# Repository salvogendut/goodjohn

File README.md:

# Goodjohn

Goodjohn is a Raspberry Pi Pico interface for using an Amstrad CPC keyboard as
a USB keyboard on a PC. This repository holds the firmware, wiring guides and
a prototype Pico carrier PCB.

> [!WARNING]
> **USB keyboard use only.** Physically disconnect the keyboard from the CPC
> motherboard before connecting it to the Pico, even if the CPC is powered off.
> **The keyboard cannot operate the CPC and the PC at the same time.** This
> interface does not provide simultaneous use or a pass-through connection to
> the CPC. Switching the CPC off is not a substitute for disconnecting it.

The first prototype uses an **original RP2040 Pico**, an **English CPC/QWERTY
keyboard**, and **exclusive control of a keyboard disconnected from the CPC
motherboard**. These are the agreed initial requirements. The passive keyboard
connects to Pico GPIO; the Pico's USB connector connects to the PC.

The drawing's **J1 adapter connector** uses the contact numbering of Bread80's
CPC464 **J3 keyboard connector**. Its square contact 1 is shown at the bottom;
labels give **GPIO / physical Pico pin**. See the [pinout sheet](docs/pinout.pdf)
for connector checks and assembly details.

**Original CPC464 PCB-style keyboard:** use the inline wiring above. Its
19-signal connector pinout is shared by rgbwalker's keyboard and Bread80's
CPC464 SMT **J3** connector. Some versions use a 20-position footprint with one
unused contact. Later CPC464 membrane keyboards use the two-ribbon connection
described below; connector orientation must still be checked on the actual board.

## Current state

There is a buildable C firmware foundation using the Raspberry Pi Pico SDK and
TinyUSB, plus native tests. It scans the physical 10-by-9 CPC464 wiring, debounces
each contact for 5 ms, and sends standard USB HID boot-keyboard reports. The
default scan period is 1 ms. Reports support six regular keys plus modifiers;
more regular keys produce HID ErrorRollOver until the count falls back to six.

Boards without diodes use conservative ghost suppression: new presses in an
ambiguous rectangle are blocked, while already accepted keys and unrelated keys
continue to work. This cannot recover arbitrary chords or detect a release that
is electrically hidden by other held keys. Fully diode-isolated boards can turn
the filter off at build time.

**Status: host tests pass; basic typing works on rgbwalker V1.2.** On 2026-10-06,
the user confirmed the complete number row (`1234567890`), all three letter rows,
Esc and main Enter with the completed 19-wire direct harness. Replacing the
earlier ribbon/jumper path resolved the incorrect characters using the existing
firmware and pin map. The exact fault in that earlier assembly is still unknown.
See the [staged wiring checks and test record](docs/wiring.md#staged-bring-up-for-rgbwalker-v12).

The remaining individual keys, modifiers, chords, cable timing, and USB
suspend/resume and current still need recorded bench tests. The carrier PCB
below is designed and checked, but has not been manufactured or bench-tested.

## Pico carrier PCB prototype

The [v1 carrier](hardware/pico-carrier-v1/README.md) is an **80 × 66 mm, two-layer
board** with a socketed RP2040 Pico, the inline 19-pin connector and separate
10-pin ribbon A/B headers. Use one keyboard through **J1 OR J2 + J3**. It keeps
the tested firmware pin map and powers the Pico through its existing USB port.

The [KiCad project](hardware/pico-carrier-v1/goodjohn-carrier.kicad_pro),
[schematic PDF](hardware/pico-carrier-v1/docs/schematic.pdf),
[assembly guide](hardware/pico-carrier-v1/docs/assembly.pdf),
[BOM](hardware/pico-carrier-v1/bom.csv) and
[Gerber/drill ZIP](hardware/pico-carrier-v1/fabrication/goodjohn-carrier-v1-gerbers.zip)
are included. ERC, DRC and schematic/PCB parity checks pass; an independent
pin-map check matches all 19 signals to the firmware and existing wiring SVGs.
**This is an unbuilt prototype, and the CPC motherboard must remain physically
disconnected.** The carrier headers accept 2.54 mm mating harnesses; bare
membrane tails need an appropriate connector adapter.

## Keyboard projects

| Project | Initial integration |
| --- | --- |
| [rgbwalker's CPC464 Cherry keyboard](https://github.com/rgbwalker/Amstrad_CPC_464_new_Cherry_Keyboard) | V1.2: digits, all letter rows, Esc and main Enter confirmed with a direct 19-wire harness. Further key/chord tests pending; retain ghost suppression. |
| [Bread80 CPC464 SMT mechanical keyboard](https://github.com/Bread80/CPC_Keyboards/tree/main/Keyswitch_CPC464_SMT) | J3 inline and J1 two-ribbon schemes traced from the KiCad PCB. J1 uses CPC464 link settings; hardware validation pending. Verified per-key diodes allow disabling ghost suppression. |
| [Bread80 tactile keyboard](https://github.com/Bread80/CPC_Keyboards/tree/main/Tactile) | Same CPC key arrangement, no diodes; connector adapter still needs checking. |
| [Bread80 CPC6128 SMT keyboard](https://github.com/Bread80/CPC_Keyboards/tree/main/Keyswitch_CPC6128_SMT) | Upstream describes this as a design-stage board; not a validated adapter target. |

Start with [the wiring notes](docs/wiring.md). Connector families are not
interchangeable just because the logical CPC matrix is the same.

For the workbench, use the [ASCII pinout sheet](docs/pinout.txt) or the
[four-page printable PDF](docs/pinout.pdf). These include the Bread80 J3 wire
list, a full Pico header diagram, assembly steps and continuity checks, plus
V1.2 connector orientation and a direct two-wire test for rgbwalker. Regenerate
both with `python3 scripts/generate_pinout.py` after installing
`scripts/requirements-docs.txt` in a Python virtual environment.
Regenerate the README's [SVG wiring diagram](docs/wiring.svg) with
`python3 scripts/generate_wiring_svg.py` in the same environment. It reuses the
Pico artwork from the supplied [pico-pinout.svg](pico-pinout.svg) and the same
firmware-derived wiring data as the sheets.

### Alternate connection: two 10-pin ribbons

Bread80's **CPC464 SMT keyboard J1**, configured for CPC464, can use two 10-way
ribbons with the existing Pico GPIO assignments. Bridge **LK1 pads 1-2** and
**LK2 pads 1-2**; leave **LK3 and the bonus links open**. This alternate harness
is source-checked and has not yet been bench-tested.

The diagram distinguishes ribbon positions from J1 PCB pad numbers. **J1 pad 19
is unused; pad 20 is connected.** Here J1 refers to Bread80's keyboard connector.
Use the [complete wiring scheme and orientation guide](docs/wiring-dual-ribbon.md),
[ASCII pinout](docs/pinout-dual-ribbon.txt), or [two-page PDF](docs/pinout-dual-ribbon.pdf).
This mapping is specific to the CPC464 setting; CPC6128 and Tactile connectors
need separate mappings. Regenerate these files with
`python3 scripts/generate_dual_ribbon.py` in the same documentation environment.

### Original CPC464 keyboard PCB

The original CPC464 keyboard PCB with the inline 19-wire connection is also
expected to work: its passive switch matrix matches the arrangement targeted
by this firmware, as shown in the
[Amstrad service manual](https://retronik.silicium.org/DOCUMENTS/Info/Amstrad_CPC/Amstrad%20CPC464%20CTM640%20GT64%20Service%20Manual.pdf).
The existing keymap should apply to the English/QWERTY version.

Disconnect the keyboard from the CPC motherboard, even when the CPC is powered
off; the Pico takes over keyboard scanning. Verify your connector's numbering,
orientation and switch continuity against the wiring notes before connecting it.
Keep `GOODJOHN_MATRIX_HAS_DIODES=OFF` (the default), since the original matrix
lacks per-key diodes and needs ghost suppression. Compatibility is expected but
has not yet been tested on original hardware; other connector revisions may
require a different harness.

## Build

Prerequisites: CMake, Make or Ninja, Python 3, an Arm bare-metal GCC toolchain
(`arm-none-eabi-gcc` and `arm-none-eabi-g++`), and the Pico SDK. A native C++
compiler is also needed if the SDK builds picotool instead of using an installed
copy. The development build was checked with SDK **2.2.0**, its pinned TinyUSB
submodule, Arm GNU **14.2.Rel1**, and picotool **2.3.1**.

For an SDK checkout outside this repository:

```sh
git clone --branch 2.2.0 --depth 1 https://github.com/raspberrypi/pico-sdk.git ../pico-sdk
git -C ../pico-sdk submodule update --init --depth 1 lib/tinyusb
cmake -S . -B build -DPICO_SDK_PATH="$(pwd)/../pico-sdk" -DPICO_BOARD=pico -DCMAKE_BUILD_TYPE=Release
cmake --build build --parallel
```

Put the compiler's `bin` directory on `PATH`, or set
`-DPICO_TOOLCHAIN_PATH=/path/to/arm-toolchain`. CMake uses an installed picotool
when available (`-Dpicotool_DIR=/path/to/picotool/cmake-directory`); otherwise the
SDK downloads and builds it, which needs network access.

The output is `build/goodjohn.uf2`. Hold BOOTSEL while connecting the Pico over
USB, then copy the UF2 to its `RPI-RP2` volume. This replaces the existing Pico
application. No hardware has been flashed as part of the initial setup.

For a board with verified diodes on every connected switch:

```sh
cmake -S . -B build -DGOODJOHN_MATRIX_HAS_DIODES=ON
cmake --build build --parallel
```

Leave this option OFF for original membranes, the rgbwalker Cherry board, and
the Bread80 tactile board. Edit `src/board_config.h` to change the GPIO wiring.

The default USB VID/PID (`CAFE:4011`) are development placeholders, not an
assignment to this project. A distributed product needs an authorized pair,
set using `GOODJOHN_USB_VID` and `GOODJOHN_USB_PID` CMake variables.

## Initial key behavior

The keymap sends PC key usages, not CPC character codes. Select the desired PC
keyboard layout in the host OS. Letters and digits follow English QWERTY, but
shifted symbols are not guaranteed to match the CPC legends.

| CPC key | PC behavior |
| --- | --- |
| DEL / CLR | Backspace / forward Delete |
| Main Enter / keypad Enter | Enter / keypad Enter |
| COPY | Left Alt |
| Either Shift | Left Shift (both switches share one matrix contact) |
| CTRL / CAPS LOCK | Left Control / Caps Lock |
| Numeric keypad | PC keypad usages; Num Lock state is controlled by the host |
| `^ £` / `- =` / `@ \|` | PC Equal / Minus / Grave key positions |
| `; +` / `: *` | PC Semicolon / Apostrophe key positions |
| Bread80 bonus switches | Unmapped initially |

There is no Fn layer yet, so F1–F12, GUI and Num Lock have no default bindings.
For early testing, set Num Lock using the PC's existing or on-screen keyboard.
The map lives in `src/keymap.c`; exact CPC symbol translation and additional
layouts are separate follow-up work. Host lock LED reports are accepted, but no
physical lock LEDs or USB remote wakeup are implemented.

## Test without a Pico SDK

```sh
cmake -S . -B build-host -DGOODJOHN_HOST_TESTS=ON
cmake --build build-host
ctest --test-dir build-host --output-on-failure
```

These tests cover contact bounce, independent debounce clocks, timer wrap,
ambiguous chords and recovery, the separate DEL column, modifier reports,
keypad Enter, and six-key overflow/recovery. They do not simulate USB hardware.

## Next hardware milestone

1. Pick the exact keyboard PCB revision and verify the connector with a meter.
2. Wire a Pico prototype and check single keys, modifiers, DEL, both Enter keys,
   press/release bounce and multi-key chords on a PC.
3. Measure scan settling with the intended cable, check suspend/resume and
   reconnect behavior, and settle the missing PC-key bindings.
4. Capture the proven wiring in an interface schematic and PCB with appropriate
   connector orientation, protection and optional lock LEDs.

## References

The adjacent keyboard projects are reference inputs and retain their respective
licenses; no upstream PCB or image assets are copied into this repository.
Exact local revisions and electrical findings are recorded in
[the wiring notes](docs/wiring.md).

Firmware references: [Pico SDK 2.2.0](https://github.com/raspberrypi/pico-sdk/tree/2.2.0),
[Raspberry Pi's USB HID example](https://github.com/raspberrypi/pico-examples/tree/master/usb/device/dev_hid_composite),
[TinyUSB](https://docs.tinyusb.org/), and
[Pico board documentation](https://www.raspberrypi.com/documentation/microcontrollers/pico-series.html).

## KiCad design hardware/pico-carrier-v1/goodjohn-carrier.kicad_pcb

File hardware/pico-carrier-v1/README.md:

# Goodjohn Pico carrier v1

An **80 × 66 mm, two-layer, hand-solderable carrier** for an original RP2040
Raspberry Pi Pico / Pico H. It replaces the tested direct jumper wiring with
PCB tracks and offers both CPC464 connector arrangements. The existing firmware
and GPIO assignments apply without changes.

**Status: unbuilt prototype.** KiCad 10.0.6 ERC and DRC pass with zero violations,
zero unconnected items and zero schematic parity issues. The actual schematic
and PCB nets also match the firmware and both existing wiring diagrams. This
PCB has not been manufactured or bench-tested; the earlier successful typing
test used a direct harness with rgbwalker V1.2.

> [!WARNING]
> **USB keyboard only. Physically disconnect the keyboard from the CPC
> motherboard, even when the CPC is powered off.** The keyboard cannot operate
> the CPC and PC simultaneously. This carrier has no switching, isolation or
> CPC pass-through circuitry. Connect one keyboard using **J1 OR J2 + J3**.

The image is a KiCad render, not a photograph of manufactured hardware.

## Files to use

- Open [goodjohn-carrier.kicad_pro](goodjohn-carrier.kicad_pro) in **KiCad 10**.
  The [schematic](goodjohn-carrier.kicad_sch), [routed PCB](goodjohn-carrier.kicad_pcb),
  project-local symbol/footprint libraries and library tables are included.
- Read the [schematic PDF](docs/schematic.pdf), [assembly PDF](docs/assembly.pdf),
  [component-side SVG](docs/assembly-top.svg) and [complete connector CSV](docs/connections.csv).
- Prototype manufacturing package:
  [Gerber + drill ZIP](fabrication/goodjohn-carrier-v1-gerbers.zip),
  [individual files](fabrication/gerbers), [fabrication notes](fabrication/README.md).
- [BOM](bom.csv), [pin-map verification](checks/pinmap.json),
  [ERC report](checks/erc.json), [DRC report](checks/drc.json).

## Connections and orientation

All three keyboard headers are ordinary **2.54 mm single-row male headers**.
Use a continuity-checked mating cable or adapter. They are not native FFC/FPC
sockets for inserting a bare original membrane tail.

With the carrier component side facing you and the Pico USB socket at the top:

| Carrier connector | Placement and pin 1 | Keyboard connection |
| --- | --- | --- |
| **U1** | Pico at left; physical pin 1 upper left, pin 40 upper right | Two 1×20 female sockets, rows 17.78 mm apart; USB faces the upper board edge |
| **J1** | 1×19 at right; **pin 1 is at the bottom**, pin 19 at the top | Inline 19-signal pinout: rgbwalker V1.2, Bread80 CPC464 SMT **J3**, original CPC464 PCB-style keyboard |
| **J2 / A** | Right-hand 1×10 ribbon header; **pin 1 at top** | Ribbon A, Bread80 keyboard **J1 odd pads** 1, 3, …, 19 |
| **J3 / B** | Left-hand 1×10 ribbon header; **pin 1 at top** | Ribbon B, Bread80 keyboard **J1 even pads** 2, 4, …, 20 |

Carrier reference names differ from keyboard reference names. **Follow contact
numbers, not apparent left-to-right order, ribbon colors or connector names.**
Match square pad 1 at both ends. The inline carrier header is intentionally
opposite in vertical numbering to the keyboard's Esc-end pin 1; a cable must
still connect contact 1 to contact 1, 2 to 2, and so on.

For Bread80's **two-ribbon J1 connection in CPC464 mode**, bridge keyboard
**LK1 pads 1–2** and **LK2 pads 1–2**; leave **LK3 and bonus links open**.
Carrier **J2.10 / A10 / keyboard J1.19 is unused**.
Carrier **J3.10 / B10 / keyboard J1.20 is required** and carries Y1.
These link settings belong to the keyboard PCB; there are no links to set on
the carrier. For the inline Bread80 J3 connection, retain the original
[inline wiring instructions](../../docs/wiring.md).

On rgbwalker V1.2 the optional twentieth contact is unused. Do not confuse that
contact with Bread80 two-ribbon J1 pad 20. Original keyboard compatibility is
expected from the pinout but has not been bench-tested. CPC6128 and Bread80
Tactile connectors are not validated targets for this carrier.

The 19 contacts carry matrix signals only. No keyboard contact connects to
ground, 3.3 V or 5 V. Ground planes join only the Pico's GND header pins.
Unused Pico GPIO, AGND, VBUS, VSYS, 3V3 and control pins have isolated pads.
The Pico receives power and exchanges data over **one USB data cable to the PC**;
no second USB port or hub is required. This simple carrier adds no input
protection or motherboard isolation; attach the harness with USB unplugged.

## Parts and assembly

The [BOM CSV](bom.csv) specifies generic mechanical requirements rather than
unverified supplier part numbers. Before buying, compare actual connector
drawings and socket height with the supplied footprints and assembly drawing.

| Item | Quantity | Specification |
| --- | ---: | --- |
| Carrier PCB | 1 | Two layers, 1.6 mm FR4, 35 µm / 1 oz copper |
| U1 module | 1 | Original RP2040 Pico with downward male headers, or Pico H; not a bare RP2040 chip |
| U1 sockets | 2 | 1×20 female, vertical, 2.54 mm pitch; 17.78 mm row spacing; nominal 8.5 mm body height |
| J1 | 1 | 1×19 male, vertical, 2.54 mm pitch, 0.64 mm square posts |
| J2, J3 | 2 | 1×10 male, vertical, 2.54 mm pitch, 0.64 mm square posts |
| Mounting hardware | Optional 4 sets | M3 standoffs/screws; 3.2 mm unplated holes; washer/head envelope ≤7 mm |
| Cables | As needed | USB data cable plus one of the two checked keyboard harnesses |

You may leave the unused keyboard connector option unpopulated. Both options
may be soldered, but only one keyboard/harness option should be plugged in.

1. Leave the Pico, keyboard and USB disconnected. Inspect the bare PCB and
   solder U1's two female sockets, keeping them parallel and flush. Fit the
   chosen keyboard headers. Pin 1 is the square pad.
2. With **U1 still removed**, check every cable end to the corresponding Pico
   socket contact using [connections.csv](docs/connections.csv). All 19 paths
   should have continuity. Different matrix nets, matrix-to-GND and
   matrix-to-power pads must remain isolated. A10 must remain isolated too.
3. Check U1 ground contacts 3, 8, 13, 18, 23, 28 and 38 have continuity with
   one another. Confirm there are no shorts between the unused supply pads.
4. Connect the detached keyboard using just one connector option. With USB
   unplugged and the Pico still removed, verify key-operated continuity using
   the table below: it appears only while the indicated key is held. Check
   the complete cable path, not only the keyboard connector.
5. Insert the Pico with its USB socket facing the board's top edge. Flash the
   existing Goodjohn UF2 via BOOTSEL if needed, then use a PC USB data cable.
   Keep ghost suppression enabled (`GOODJOHN_MATRIX_HAS_DIODES=OFF`) unless
   the attached keyboard's diode arrangement has been verified.
6. Record Esc, digits, letters, Enter, Space, DEL, modifiers and chords in a
   text editor. The two-ribbon board and original keyboard still need actual
   hardware validation; record the board version and harness used.

| Key | Inline carrier contacts | Two-ribbon carrier contacts | Pico physical contacts |
| --- | --- | --- | --- |
| Top-row 1 | J1.3 + J1.11 | J2.2 + J3.2 | 16 + 14 |
| Top-row 2 | J1.4 + J1.11 | J2.3 + J3.2 | 17 + 14 |
| Esc | J1.5 + J1.11 | J2.4 + J3.2 | 19 + 14 |
| Main Enter | J1.5 + J1.17 | J2.4 + J3.8 | 19 + 6 |
| Space | J1.10 + J1.14 | J3.1 + J3.5 | 25 + 10 |
| DEL / USB Backspace | J1.1 + J1.2 | J2.9 + J2.1 | 26 + 15 |

Diode-equipped keyboards may require the meter's diode-test mode and correct
probe polarity instead of a continuity beep.

## Mechanical details

Board outline: **80 × 66 mm**, four straight edges, no panelization. Hole
centres measured from the upper-left board corner are **(4,4), (76,4),
(4,62), (76,62) mm**. All four holes are 3.2 mm NPTH; 7 × 7 mm areas around
them exclude tracks, vias and copper pours. This layout has no CPC case fit
claim. Insulate the underside from metalwork and support the board on standoffs.

Pico socket pin 1 is at (10.16, 3.048) mm from that corner; the second socket
row is 17.78 mm to the right. The Pico USB connector faces outwards near the
top edge. Verify the chosen cable plug and socket stack height during the
first physical assembly; the 3D library model is illustrative.

## Editing and rebuilding outputs

The committed `.kicad_sch` and `.kicad_pcb` are the editable design authority.
Use KiCad's normal editors and Update PCB from Schematic for further changes.
Local symbol and footprint libraries make the design independent of sibling
repositories. Standard KiCad 10 3D libraries are needed only for 3D viewing.

See [the hardware tooling instructions](../tools/README.md) for validation,
export and regeneration. Placement was generated with KiCad's Python API and
routed locally with Freerouting **2.5.0**; the final board includes a ground
stitching via at board coordinates (119,120) mm to join a copper strip.
There are 13 vias, all 0.8 / 0.4 mm, and 0.30 mm signal tracks. Minimum design
clearance is 0.25 mm; the router used 0.30 mm. Neither ERC nor DRC suppresses
violations with exclusions.

Pinout provenance and previous bench evidence remain in the repository's
[inline](../../docs/wiring.md) and [two-ribbon](../../docs/wiring-dual-ribbon.md)
notes. Module mechanics come from the
[Raspberry Pi Pico datasheet](https://datasheets.raspberrypi.com/pico/pico-datasheet.pdf)
and the KiCad footprint; [library attribution and changes](libraries/README.md)
are recorded separately. See the [validation record](checks/README.md) for the
checks completed and the remaining physical prototype work.

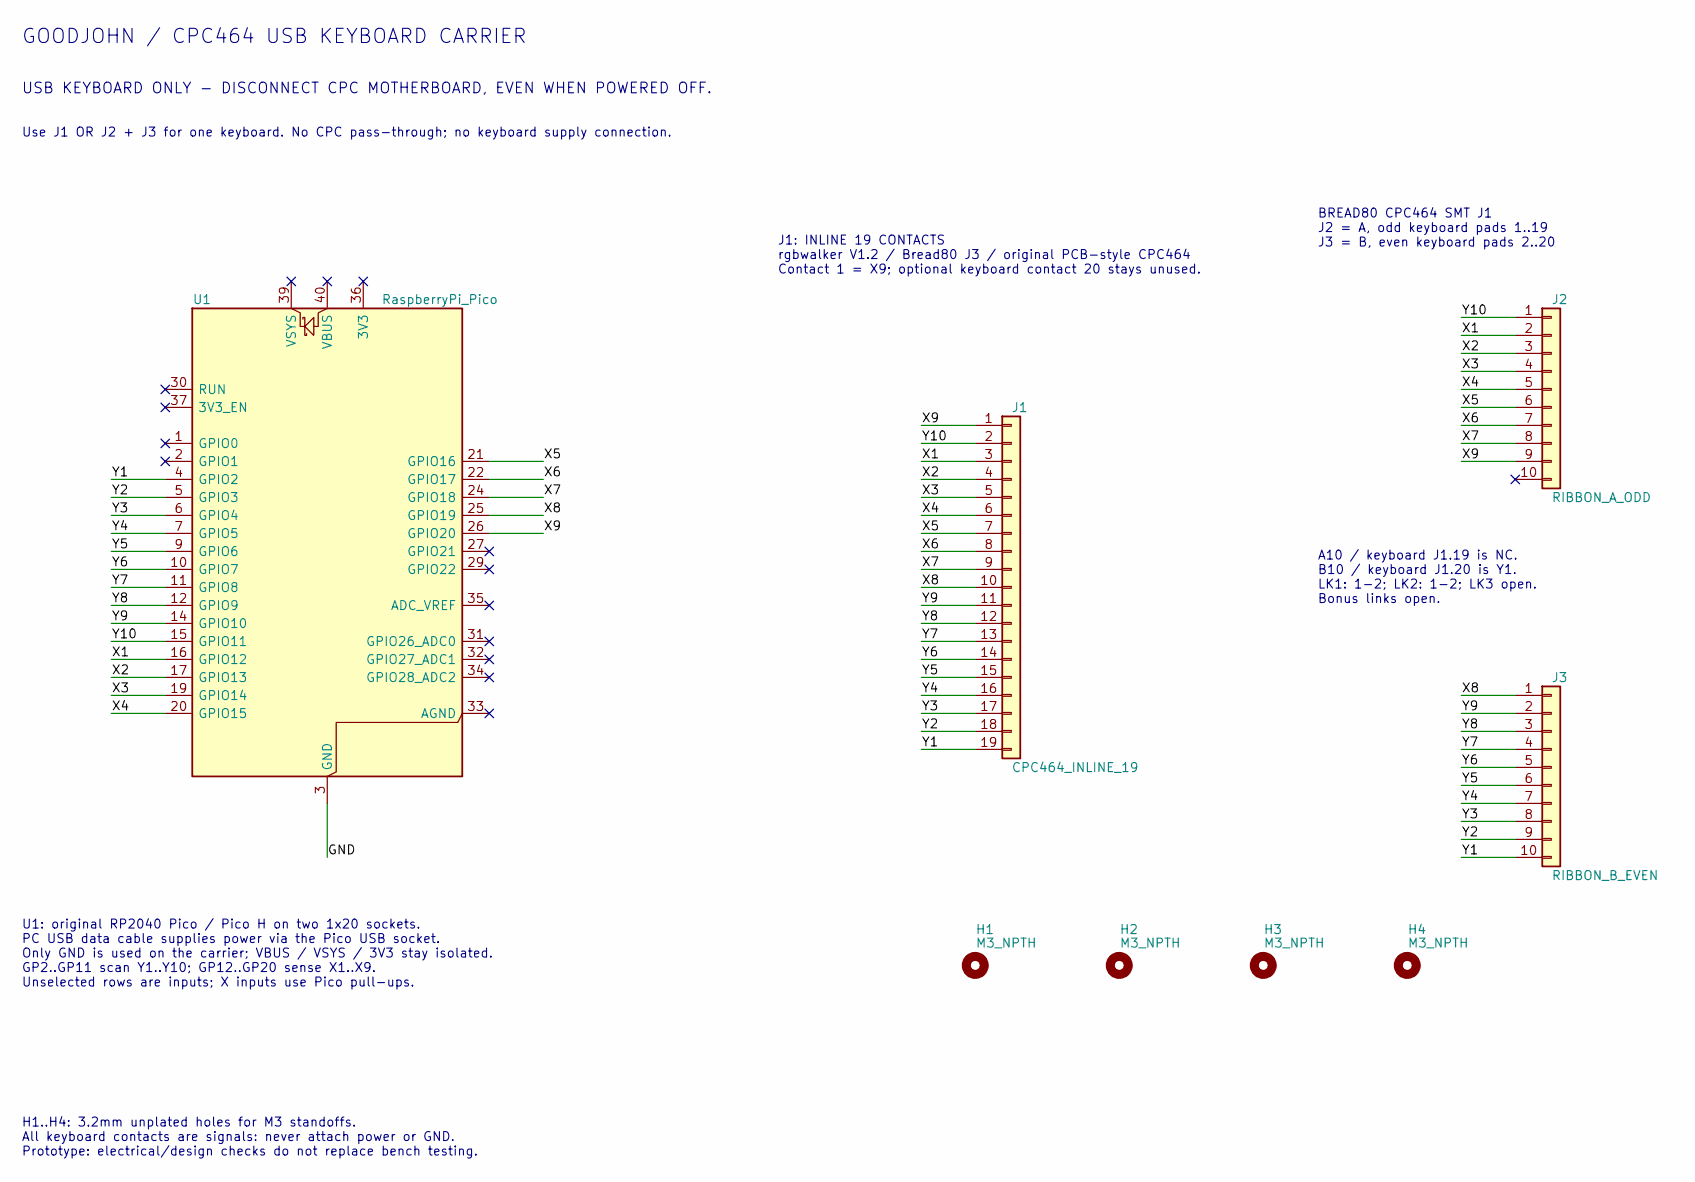
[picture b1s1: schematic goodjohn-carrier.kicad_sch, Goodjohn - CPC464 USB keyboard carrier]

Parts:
H1, H2, H3, H4: M3_NPTH; MountingHole_3.2mm_M3
J1: CPC464_INLINE_19; PinHeader_1x19_P2.54mm_Vertical
J2: RIBBON_A_ODD; PinHeader_1x10_P2.54mm_Vertical
J3: RIBBON_B_EVEN; PinHeader_1x10_P2.54mm_Vertical
U1: RaspberryPi_Pico; Pico_Socketed_RP2040

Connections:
/GND: U1.3 (GND), U1.8 (GND), U1.13 (GND), U1.18 (GND), U1.23 (GND), U1.28 (GND), U1.38 (GND)
/X1: J1.3, J2.2, U1.16 (GPIO12)
/X2: J1.4, J2.3, U1.17 (GPIO13)
/X3: J1.5, J2.4, U1.19 (GPIO14)
/X4: J1.6, J2.5, U1.20 (GPIO15)
/X5: J1.7, J2.6, U1.21 (GPIO16)
/X6: J1.8, J2.7, U1.22 (GPIO17)
/X7: J1.9, J2.8, U1.24 (GPIO18)
/X8: J1.10, J3.1, U1.25 (GPIO19)
/X9: J1.1, J2.9, U1.26 (GPIO20)
/Y1: J1.19, J3.10, U1.4 (GPIO2)
/Y2: J1.18, J3.9, U1.5 (GPIO3)
/Y3: J1.17, J3.8, U1.6 (GPIO4)
/Y4: J1.16, J3.7, U1.7 (GPIO5)
/Y5: J1.15, J3.6, U1.9 (GPIO6)
/Y6: J1.14, J3.5, U1.10 (GPIO7)
/Y7: J1.13, J3.4, U1.11 (GPIO8)
/Y8: J1.12, J3.3, U1.12 (GPIO9)
/Y9: J1.11, J3.2, U1.14 (GPIO10)
/Y10: J1.2, J2.1, U1.15 (GPIO11)

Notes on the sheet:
GOODJOHN / CPC464 USB KEYBOARD CARRIER
USB KEYBOARD ONLY - DISCONNECT CPC MOTHERBOARD, EVEN WHEN POWERED OFF.
Use J1 OR J2 + J3 for one keyboard. No CPC pass-through; no keyboard supply connection.
U1: original RP2040 Pico / Pico H on two 1x20 sockets. PC USB data cable supplies power via the Pico USB socket. Only GND is used on the carrier; VBUS / VSYS / 3V3 stay isolated. GP2..GP11 scan Y1..Y10; GP12..GP20 sense X1..X9. Unselected rows are inputs; X inputs use Pico pull-ups.
J1: INLINE 19 CONTACTS rgbwalker V1.2 / Bread80 J3 / original PCB-style CPC464 Contact 1 = X9; optional keyboard contact 20 stays unused.
BREAD80 CPC464 SMT J1 J2 = A, odd keyboard pads 1..19 J3 = B, even keyboard pads 2..20
A10 / keyboard J1.19 is NC. B10 / keyboard J1.20 is Y1. LK1: 1-2; LK2: 1-2; LK3 open. Bonus links open.
H1..H4: 3.2mm unplated holes for M3 standoffs. All keyboard contacts are signals: never attach power or GND. Prototype: electrical/design checks do not replace bench testing.

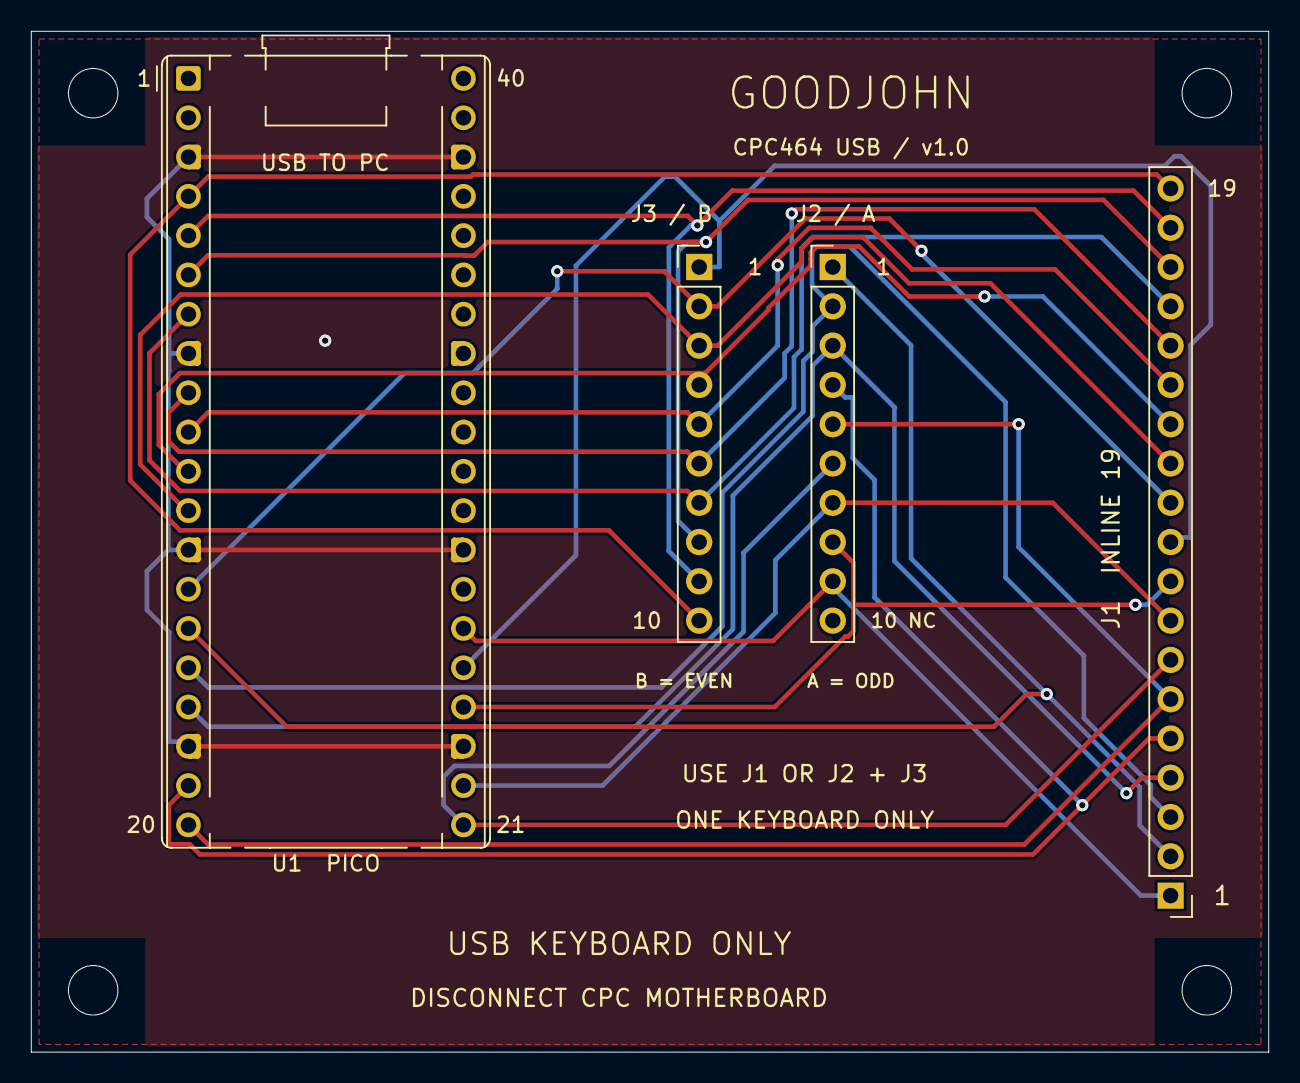
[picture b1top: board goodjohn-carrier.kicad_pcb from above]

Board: 2 copper layers, 80.0 x 66.0 mm, 8 parts (0 on the bottom side), 20 nets.
